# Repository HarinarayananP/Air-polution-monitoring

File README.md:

# Polmo - Air Pollution Monitoring System

POLMO is a low cost IoT based real time air pollution monitoring system. It uses advanced sensing technologies to collect pollution information from the real world sensors and provides real time data visualization, machine learning based air quality prediction, warning information for human beings, animals, and plants due to air pollution.
## Contents

- [Polmo - Air Pollution Monitoring System](#polmo---air-pollution-monitoring-system)
  - [Contents](#contents)
  - [Short description](#short-description)
    - [What's the problem?](#whats-the-problem)
    - [How can technology help?](#how-can-technology-help)
    - [The idea](#the-idea)
  - [Demo video](#demo-video)
  - [The architecture](#the-architecture)
  - [Long description](#long-description)
  - [Project roadmap](#project-roadmap)
  - [Getting started](#getting-started)
  - [Live demo](#live-demo)
  - [Applications](#applications)
    - [Mesh Network - Simple application](#mesh-network---simple-application)
    - [Mesh Network - Vehicle Traffic](#mesh-network---vehicle-traffic)
  - [Built with](#built-with)
  - [Contributing](#contributing)
  - [Authors](#authors)
  - [License](#license)
  - [Acknoledgement](#acknoledgement)

## Short description

### What's the problem?

Air pollution adversely affects human health, plant life, and agricultural crop production. Agricultural crops can be injured when exposed to high concentrations of various air pollutants. In a recent study, researchers have analysed 30 years of data on yields of wheat and rice alongside data on air pollution and climate in India and concluded that significant decreases in yield could be attributed to air pollutants.

### How can technology help?

Regular monitoring and controlling air pollution leads to increased yield from agricultural and livestock products. The warning can be given to farmers using pollution related predictions, precautions can be taken to protect plants, plan for the right cultivation time to get more yield.  There is an increased demand for localized IoT enabled automated air pollution monitoring systems which provide air pollution related information for people through an easy interface.  For realizing such a system gas sensors with advanced sensing technologies, IoT, cloud computing, and machine learning can be Incorporated.

### The idea

Developing and deploying low cost, low power, quicker, and real time air pollution monitoring system at pollution affected area. For this, array sensor nodes are developed by incorporating major air pollutants sensors and NodeMCU.  This embedded system uploads the air pollution data to the IBM Watson IoT cloud over Wi-Fi protocol. 

## Demo video

## The architecture

1. Node Mcu from Polmo sensor node reads the sensor readings. 
2. It will send the readings through MQTT Protocol to IBM Watson IOT
3. Using Node Red Flows the readings are fetched from IBM Watson IOT and Stored it into IBM Cloudant DB
4. A public API Endpoint is made using Fast API, It processes and delivers the contents from Cloudant DB to Apps
5. A React Dashboard is created to visualize realtime data.

## Long description

[More detail is available here](./docs/DESCRIPTION.md)

## Project roadmap

The project currently does the following things.
- Sense Major Pollutants.
- Sent readings seperatly to IBM Watson IOT cloud.
- Display Realtime data at Webendpoint
- Provide API to fetch Realtime and historical data.

See below for our past road map before Call for Code 2021 submission.

## Getting started

You can find the details of each section by clicking the image 🖼️ below 🔻 .

## Live demo

By clicking this [link you](https://polmo-react-app.vercel.app/) can visit the live website. 

## Applications
Here are some animations which we are planning to build. 
### Mesh Network - Simple application

### Mesh Network - Vehicle Traffic

## Built with

- [IBM Cloudant](https://cloud.ibm.com/catalog?search=cloudant#search_results) - The NoSQL database used
- [IBM Watson IOT](https://cloud.ibm.com/catalog?search=IOT#search_results) - The Internet of things platform
- [IBM Cloud Foundry](https://cloud.ibm.com/catalog?search=cloud%20foundry#search_results) - The Application Containers

## Contributing

Please read [CONTRIBUTING.md](CONTRIBUTING.md) for details on our code of conduct, and the process for submitting pull requests to us.

## Authors

- **Harinarayanan P** - [GitHub](https://github.com/HarinarayananP)
- **Amjed Ali K** - [GitHub](https://github.com/amjed-ali-k)
- **Sukhdev K** - [GitHub](https://github.com/Sukhdev)

## License

This project is licensed under the Apache 2 License - see the [LICENSE](LICENSE) file for details.

## Acknoledgement

We sincerly inform our gratitudes to
- [Sebastián Ramírez] (https://github.com/tiangolo) - For FastAPI framework
- [Creative Tim] (https://www.creative-tim.com/) - For Argon free dashboard template
- [Webkom] (https://github.com/0wczar/airframe-react) - For a beautiful react Dashboard
- [Freepik] (https://freepik.com) - For design files and templates
- All family, friends, collegues who helped and appreciated us in this journey.

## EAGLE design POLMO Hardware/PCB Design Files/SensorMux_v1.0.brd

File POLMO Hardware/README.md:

# POLMO - Hardware

## Contents
- [POLMO - Hardware](#polmo---hardware)
  - [Contents](#contents)
  - [Code](#code)
  - [Hardware Photo](#hardware-photo)
  - [Designs of Multiple node](#designs-of-multiple-node)
    - [Polmo Rural node](#polmo-rural-node)
    - [Polmo Urban node](#polmo-urban-node)
    - [Indoor Closed Network Polmo node](#indoor-closed-network-polmo-node)

## Code
Node Mcu (ESP8266 1.0) code can be viewed by clicking this [link](./Node%20Mcu%20Code/mqttclient.ino).
You have to update the WiFi credentials in the code shown below.

```cpp
// WiFi Credentials
const char* ssid = "********"; // WiFi SSID
const char* password = "**************"; // WiFi Password
```
Also IBM Watson IOT configshown below.
```cpp
// IBM Watson IOT - Device Credentials
#define ORG "****" 
#define DEVICE_TYPE "*******" 
#define DEVICE_ID "****" 
#define TOKEN "**********" 

```
This code use Non-Secure data communitication. So, after updating the code, Kindly disable the security to Token Authentication on IBM Watson IOT Dashboard.

## Hardware Photo
Below shows the photo of Hardware prototype which we made for testing.
The PCB Design and Schematic Diagrams can be found [here.](/PCB%20Design%20Files)

## Designs of Multiple node
Here show multiple data flow designs for individual Polmo nodes we are going to fabricate. Currently the node connects directly to the IBM Watson IOT platform. But when we scale the nodes into multiple areas or creating a mesh network, All data flow goes through a master node. LoraWan or any other low power networks will be used to connect between Polmo End Nodes and Master nodes. Master nodes will be connected directly to IBM Watson IOT Platform.
Depending upon the type of region, envornaments we have to design and implement diffrent types of end nodes. Mainly there are 3 types of Polmo End nodes
- Polmo Rural node - For Villages, Farmlands, Green Terrains.
- Polmo Urban node - For Cities, Industiral, Crouded areas.
- Polmo Indoor node - For Homes, Factories, Large camps, Reserved areas.

### Polmo Rural node
This node is indented to deploy in less areas like villages, farmlands. There will be only limited number of deployments in a large area. Sensors will only collect data in long intervals and go to sleep mode. Long range low power communication protocols like LoRaWAN will be used to connect this nodes to its master.
<br><br>

### Polmo Urban node
Polmo Urban nodes will be deployed in highly populated, crouded areas where pollution will affect large number of beings. This node will fetch sensor readings in seconds and send to its master node. Urban nodes will be deployed in short range and even a single city will contains multiple nodes. Urban nodes will have much more accuracy and used to display realtime readings.
<br><br>

### Indoor Closed Network Polmo node
Indoor nodes are made for deployment inside homes, factories and industries. It will be used for particular purposes and safety of humans in houses and the workers in factory. These nodes may not have master nodes and will be directly connected to LAN networks. 
<br><br>

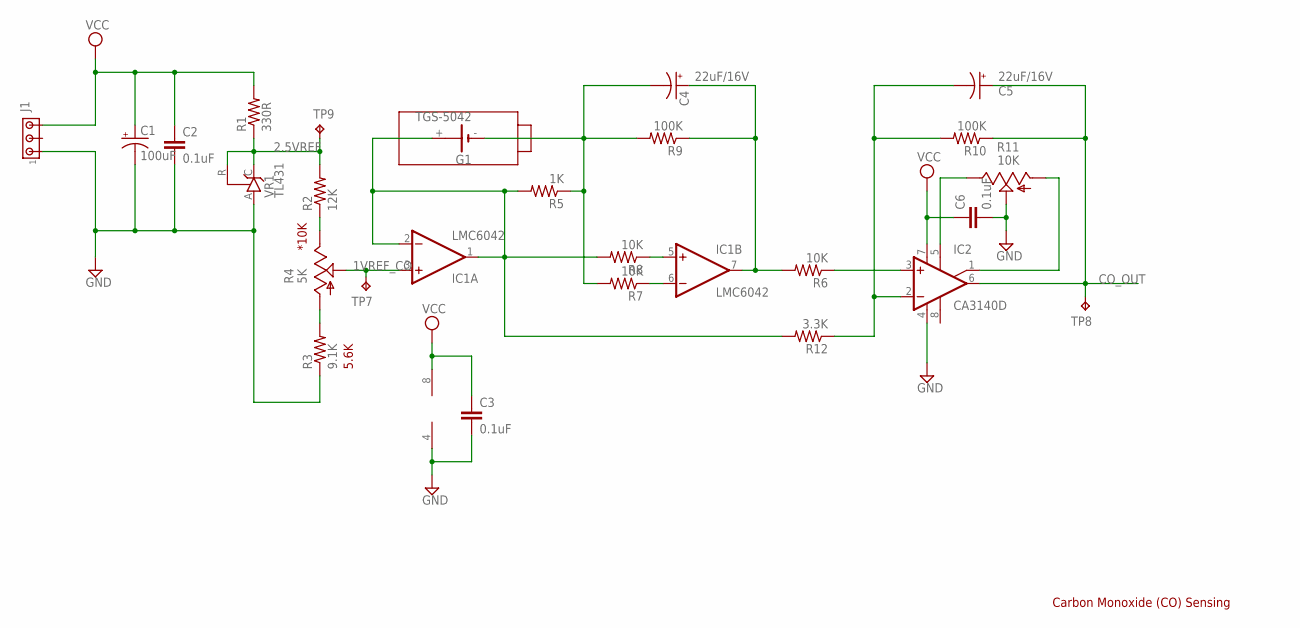
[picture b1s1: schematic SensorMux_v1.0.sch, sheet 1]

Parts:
C1: 100uF; E5-6
C2, C3, C6: 0.1uF; C0603K
C4, C5: 22uF/16V; E2,5-6
G1: TGS-5042; CRAA
IC1: LMC6042; SO08
IC2: CA3140D; SO08
J1: MTA03-100; 10X03MTA
R1: 330R; R0805
R2: 12K; R0805
R3: 9.1K; R0805
R4: 5K; B64Y
R5: 1K; R0805
R6, R7, R8: 10K; R0805
R9, R10: 100K; R0805
R11: 10K; B64Y
R12: 3.3K; R0805
TP7: 1V; TP08R
TP8: CO; TP08R
TP9: 2.5V; TP08R
VR1: TL431; TO92-CLP

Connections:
1VREF_CO: IC1.3 (+IN), R4.S, TP7.TP
2.5VREF: R1.1, R2.2, TP9.TP, VR1.C, VR1.R; also elsewhere on the board
CO_OUT: C5.+, IC2.6 (OUT), R10.1, TP8.TP; also elsewhere on the board
GND: C1.-, C2.2, C3.2, C6.2, IC1.4 (V-), IC2.4 (V-), J1.1, R3.1, R11.S, VR1.A; also elsewhere on the board
unnamed: G1.+, IC1.1 (OUT), IC1.2 (-IN), R5.2, R8.2, R12.2
unnamed: IC1.6 (-IN), R7.1
unnamed: C4.-, G1.-, R5.1, R7.2, R9.2
unnamed: IC1.5 (+IN), R8.1
unnamed: R2.1, R4.E
unnamed: R3.2, R4.A
unnamed: C4.+, IC1.7 (OUT), R6.2, R9.1
unnamed: IC2.3 (+IN), R6.1
unnamed: C5.-, IC2.2 (-IN), R10.2, R12.1
unnamed: IC2.5 (ON), R11.E
unnamed: IC2.1 (ON/CMP), R11.A
VCC: C1.+, C2.1, C3.1, C6.1, IC1.8 (V+), IC2.7 (V+), J1.3, R1.2; also elsewhere on the board

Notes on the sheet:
Carbon Monoxide (CO) Sensing
5.6K
*10K

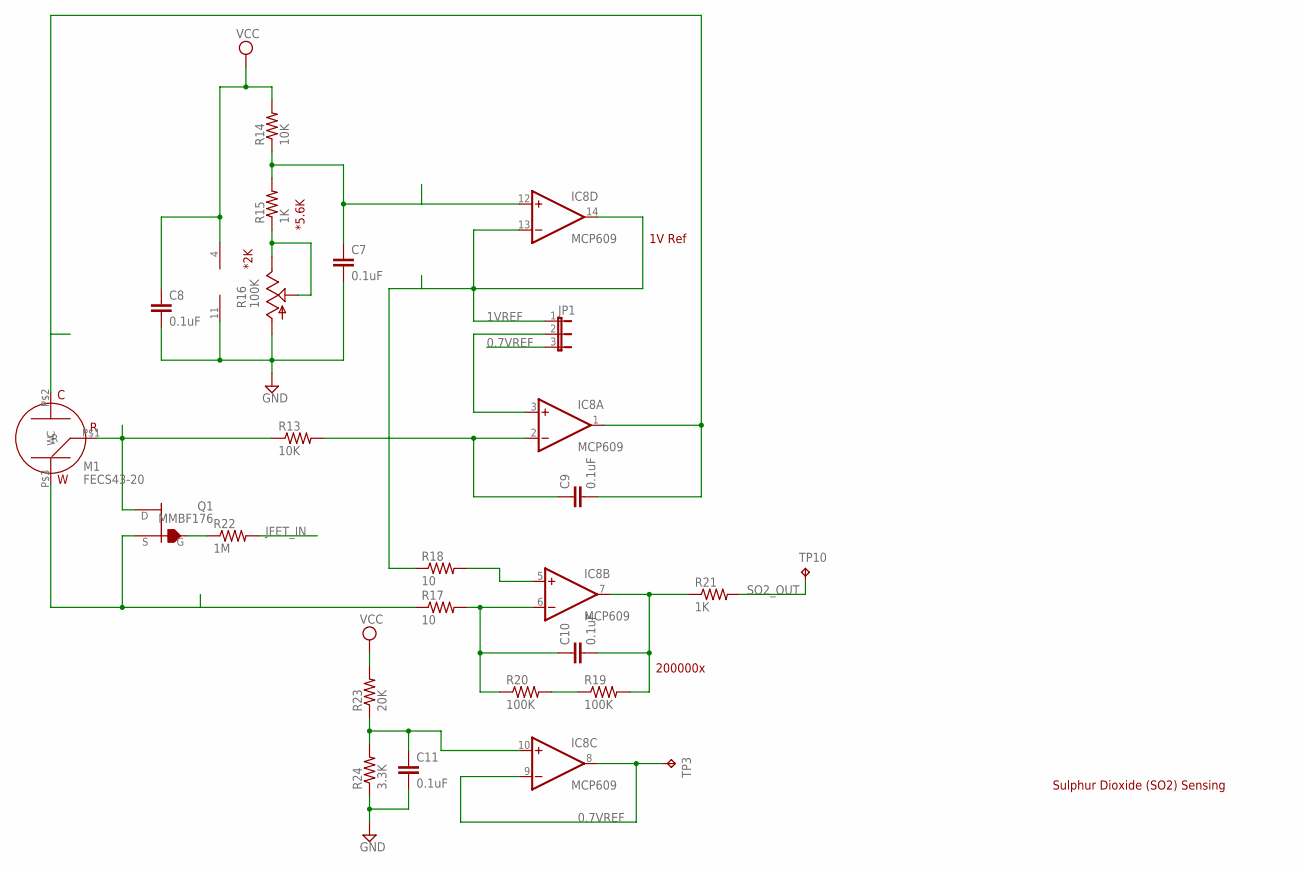
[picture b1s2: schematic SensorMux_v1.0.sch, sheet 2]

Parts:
C7, C8, C9, C10, C11: 0.1uF; C0603K
IC8: MCP609; SO14
JP1: JP2E; JP2
M1: FECS43-20; FECS43
Q1: MMBF176; SOT23
R13: 10K; R0603
R14: 10K; R0805
R15: 1K; R0805
R16: 100K; B64Y
R17, R18: 10; R0603
R19, R20: 100K; R0603
R21: 1K; R0603
R22: 1M; R0603
R23: 20K; R0805
R24: 3.3K; R0805
TP3: 0.7V; TP08R
TP10: SO2; TP08R

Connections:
0.7V: C11.1, IC8.10 (+IN), R23.1, R24.2
0.7VREF: IC8.8 (OUT), IC8.9 (-IN), JP1.3, TP3.TP
1VREF: IC8.13 (-IN), IC8.14 (OUT), JP1.1, R18.1
GND: C7.2, C8.2, C11.2, IC8.11 (V-), R16.A, R24.1; also elsewhere on the board
JFET_IN: R22.2; also elsewhere on the board
unnamed: C9.1, IC8.2 (-IN), R13.2
unnamed: M1.P$1 (R), Q1.1 (D), R13.1
unnamed: C9.2, IC8.1 (OUT), M1.P$2 (C)
unnamed: R15.1, R16.E, R16.S
unnamed: R19.1, R20.2
unnamed: C7.1, IC8.12 (+IN), R14.1, R15.2
unnamed: IC8.3 (+IN), JP1.2
unnamed: C10.1, IC8.6 (-IN), R17.2, R20.1
unnamed: IC8.5 (+IN), R18.2
unnamed: M1.P$3 (W), Q1.2 (S), R17.1
unnamed: C10.2, IC8.7 (OUT), R19.2, R21.1
unnamed: Q1.3 (G), R22.1
SO2_OUT: R21.2, TP10.TP; also elsewhere on the board
VCC: C8.1, IC8.4 (V+), R14.2, R23.2; also elsewhere on the board

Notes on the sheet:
1V Ref
200000x
Sulphur Dioxide (SO2) Sensing
*5.6K
*2K

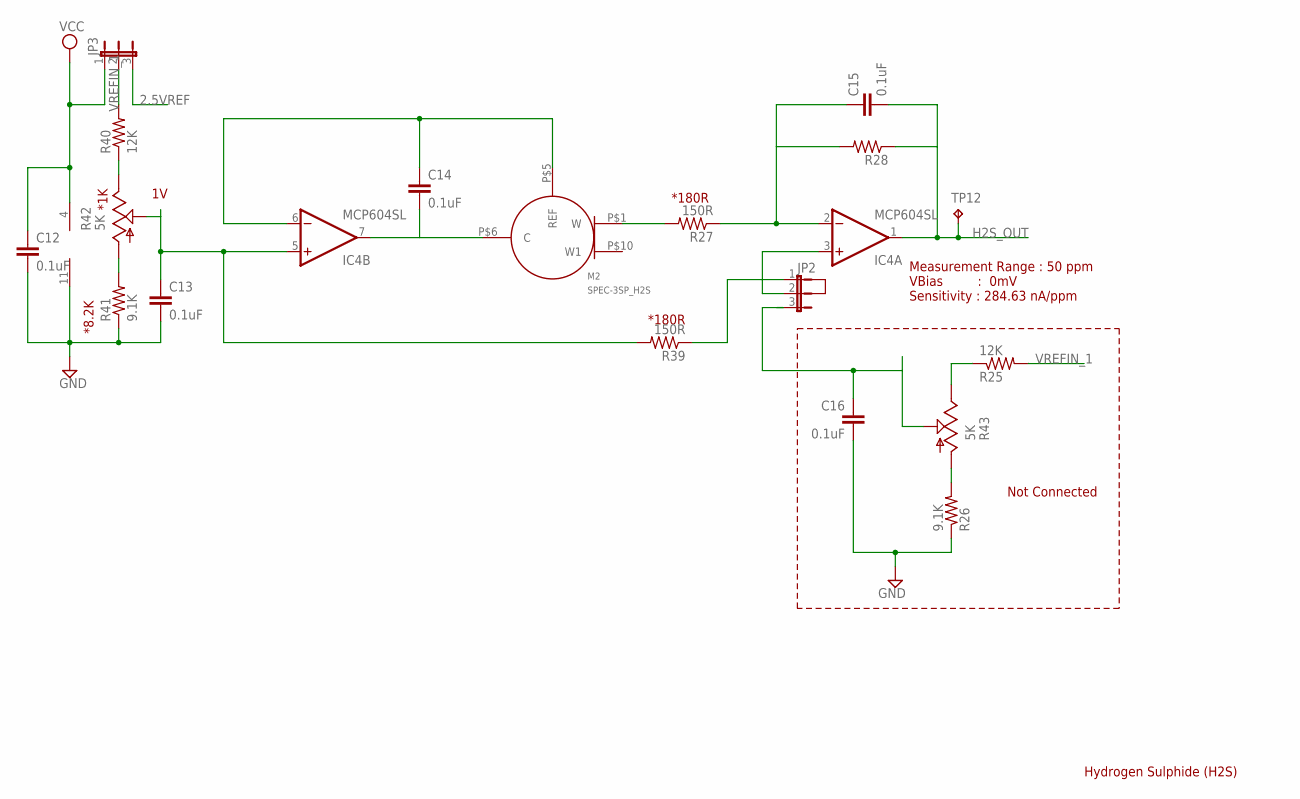
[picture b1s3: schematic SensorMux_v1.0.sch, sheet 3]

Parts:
C12, C13, C14, C15, C16: 0.1uF; C0603K
IC4: MCP604SL; SO14
JP2, JP3: JP2E; JP2
M2: SPEC-3SP_H2S; SPEC-3SP
R25, R40: 12K; R0805
R26, R41: 9.1K; R0805
R27, R39: 150R; R0805
R28: R-US_R0805; R0805
R42, R43: 5K; B64Y
TP12: H2S; TP08R

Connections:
2.5VREF: JP3.3; also elsewhere on the board
GND: C12.2, C13.2, C16.2, IC4.11 (V-), R26.1, R41.1; also elsewhere on the board
H2S_OUT: C15.2, IC4.1 (OUT), R28.1, TP12.TP; also elsewhere on the board
unnamed: C14.1, IC4.6 (-IN), M2.P$5 (REF)
unnamed: C14.2, IC4.7 (OUT), M2.P$6 (C)
unnamed: C13.1, IC4.5 (+IN), R39.2, R42.S
unnamed: M2.P$1 (W), R27.2
unnamed: C15.1, IC4.2 (-IN), R27.1, R28.2
unnamed: C16.1, JP2.3, R43.S
unnamed: IC4.3 (+IN), JP2.2
unnamed: R25.1, R43.E
unnamed: R26.2, R43.A
unnamed: JP2.1, R39.1
unnamed: R40.1, R42.E
unnamed: R41.2, R42.A
VCC: C12.1, IC4.4 (V+), JP3.1; also elsewhere on the board
VREFIN_1: JP3.2, R25.2, R40.2

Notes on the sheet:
Hydrogen Sulphide (H2S)
Measurement Range : 50 ppm VBias : 0mV Sensitivity : 284.63 nA/ppm
*180R
*8.2K
*1K
Not Connected

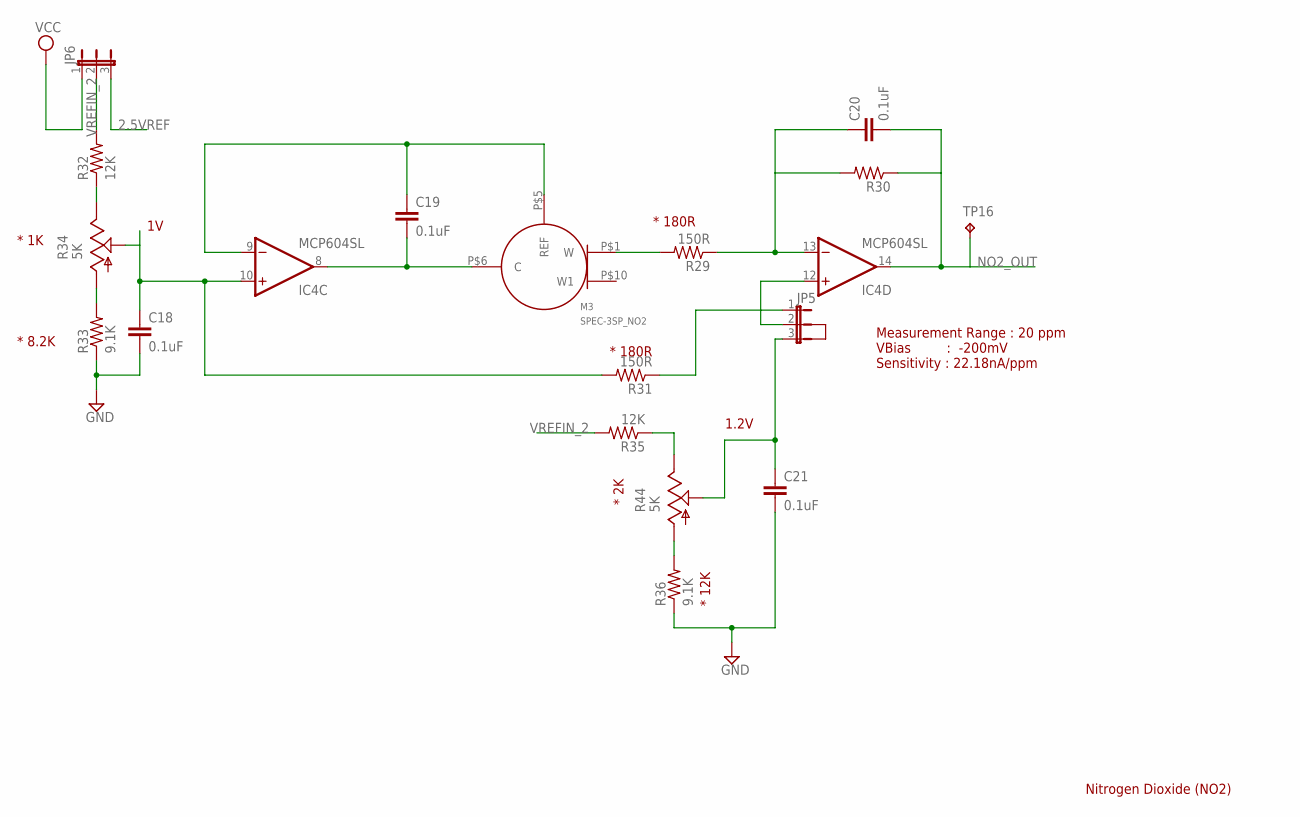
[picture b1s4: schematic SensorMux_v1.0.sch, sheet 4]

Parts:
C18, C19, C20, C21: 0.1uF; C0603K
IC4: MCP604SL; SO14
JP5, JP6: JP2E; JP2
M3: SPEC-3SP_NO2; SPEC-3SP
R29, R31: 150R; R0805
R30: R-US_R0805; R0805
R32, R35: 12K; R0805
R33, R36: 9.1K; R0805
R34, R44: 5K; B64Y
TP16: NO2; TP08R

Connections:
2.5VREF: JP6.3; also elsewhere on the board
GND: C18.2, C21.2, R33.1, R36.1; also elsewhere on the board
unnamed: C19.1, IC4.9 (-IN), M3.P$5 (REF)
unnamed: C19.2, IC4.8 (OUT), M3.P$6 (C)
unnamed: C18.1, IC4.10 (+IN), R31.2, R34.S
unnamed: M3.P$1 (W), R29.2
unnamed: C20.1, IC4.13 (-IN), R29.1, R30.2
unnamed: C21.1, JP5.3, R44.S
unnamed: IC4.12 (+IN), JP5.2
unnamed: JP5.1, R31.1
unnamed: R32.1, R34.E
unnamed: R33.2, R34.A
unnamed: R35.1, R44.E
unnamed: R36.2, R44.A
NO2_OUT: C20.2, IC4.14 (OUT), R30.1, TP16.TP; also elsewhere on the board
VCC: JP6.1; also elsewhere on the board
VREFIN_2: JP6.2, R32.2, R35.2

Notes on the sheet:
Nitrogen Dioxide (NO2)
Measurement Range : 20 ppm VBias : -200mV Sensitivity : 22.18nA/ppm
* 1K
* 8.2K
* 12K
* 2K
1.2V
* 180R

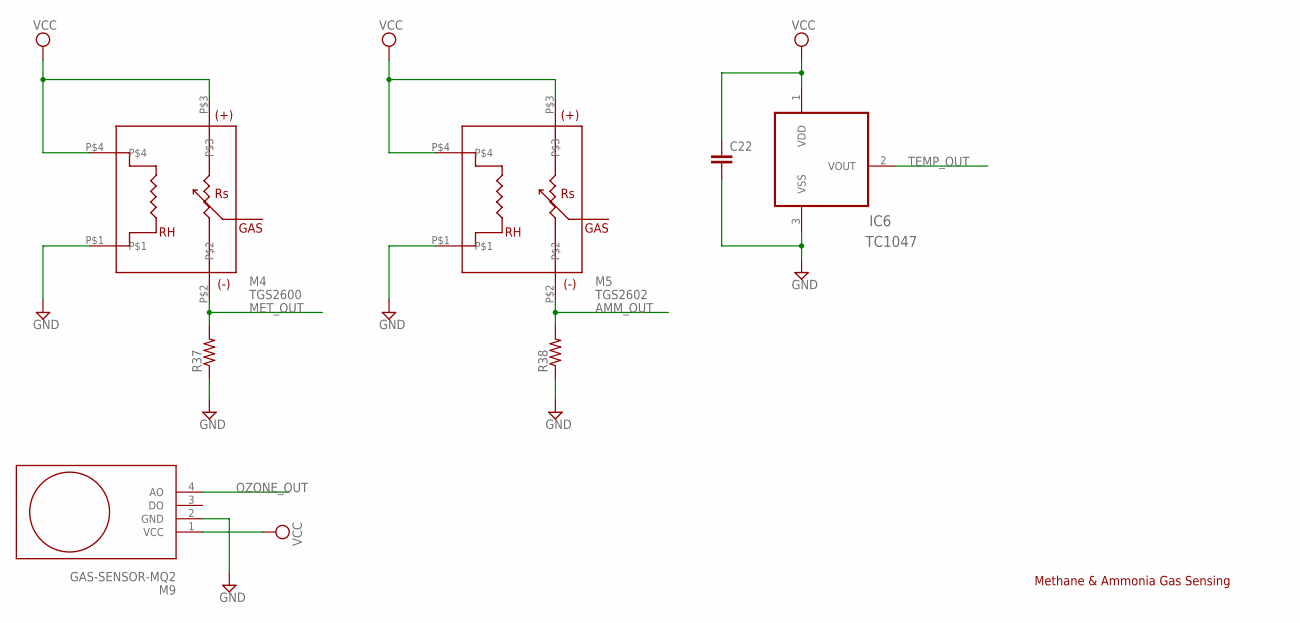
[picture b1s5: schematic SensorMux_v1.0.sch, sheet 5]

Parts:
C22: C-EUC0603K; C0603K
IC6: TC1047; SOT95P237X112-3N
M4: TGS2600; TGS26XX
M5: TGS2602; TGS26XX
M9: GAS-SENSOR-MQ2
R37, R38: R-US_M0805; M0805

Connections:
AMM_OUT: M5.P$2, R38.2; also elsewhere on the board
GND: C22.2, IC6.3 (VSS), M4.P$1, M5.P$1, M9.2 (GND), R37.1, R38.1; also elsewhere on the board
MET_OUT: M4.P$2, R37.2; also elsewhere on the board
OZONE_OUT: M9.4 (AO); also elsewhere on the board
TEMP_OUT: IC6.2 (VOUT); also elsewhere on the board
VCC: C22.1, IC6.1 (VDD), M4.P$3, M4.P$4, M5.P$3, M5.P$4, M9.1 (VCC); also elsewhere on the board

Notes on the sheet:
Methane & Ammonia Gas Sensing

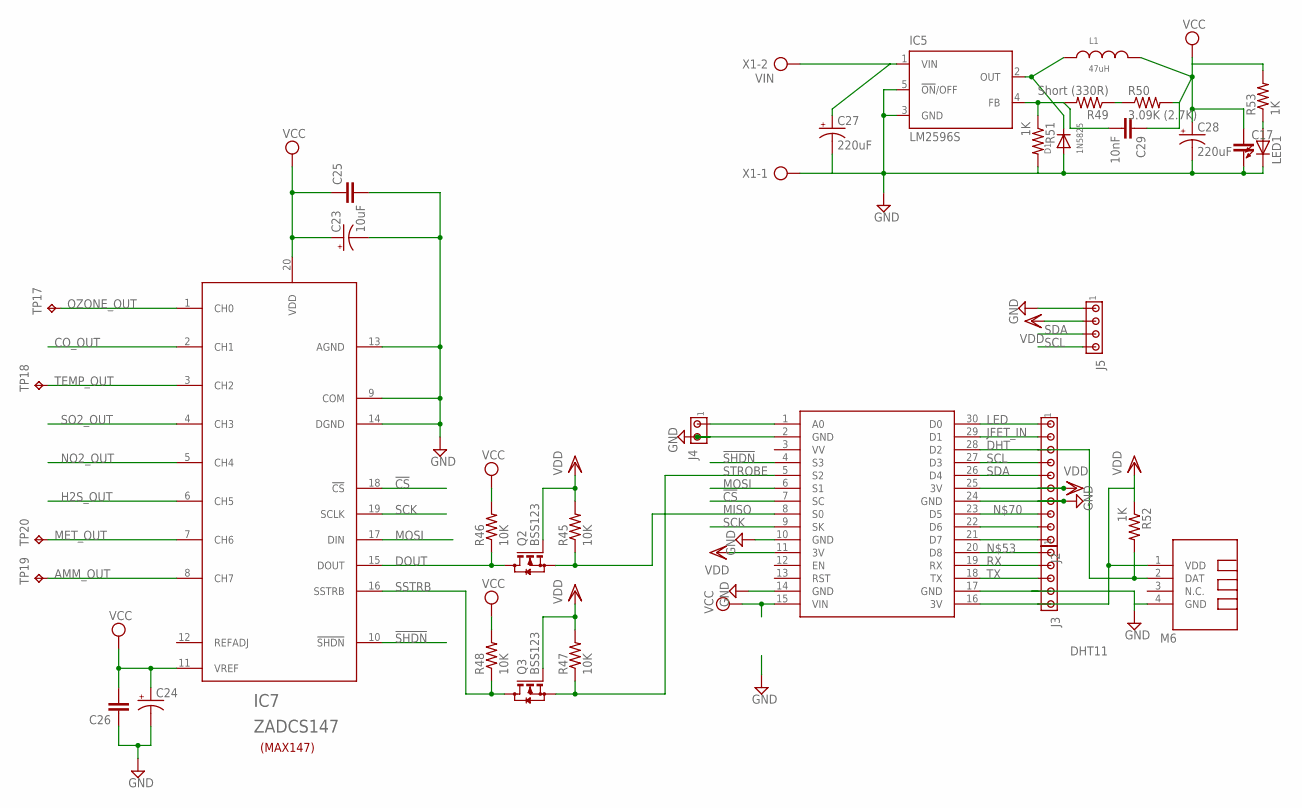
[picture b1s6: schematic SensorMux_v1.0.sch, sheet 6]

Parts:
C17, C25, C26: C-EUC0603K; C0603K
C23: 10uF; SMC_A
C24: CPOL-USSMCA; SMC_A
C27, C28: 220uF; 140CLH-0810
C29: 10nF; C0603K
D1: 1N5825; SMADIODE
IC5: LM2596S; TO263-5
IC7: ZADCS147; SSOP20
J2: MTA10-100; 10X10MTA
J3: MTA05-100; 10X05MTA
J4: MTA02-100; 10X02MTA
J5: MTA04-100; 10X04MTA
L1: 47uH; WE-CHSA_1212
LED1: LED3MM
M6: DHT11; TEMP-HUM-SENSOR-DHT11
M8: NODEMCU
Q2, Q3: BSS123; SOT23
R45, R46, R47, R48: 10K; R0603
R49: Short (330R); R0603
R50: 3.09K (2.7K); R0603
R51, R52, R53: 1K; R0603
TP17: Ozone; TP08R
TP18: Temp; TP08R
TP19: AMM; TP08R
TP20: MET; TP08R
X1: VIN; AK500/2

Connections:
!CS: IC7.18 (!CS), M8.7 (SC)
!SHDN: IC7.10 (!SHDN), M8.4 (S3)
AMM_OUT: IC7.8 (CH7), TP19.TP; also elsewhere on the board
CO_OUT: IC7.2 (CH1); also elsewhere on the board
DHT: J2.3, M6.2 (DAT), M8.28 (D2), R52.2
DOUT: IC7.15 (DOUT), Q2.3 (D), R46.1
GND: C17.2, C23.-, C24.-, C25.2, C26.1, C27.-, C28.-, D1.A, IC5.3 (GND), IC5.5 (!ON!/OFF), IC7.9 (COM), IC7.13 (AGND), IC7.14 (DGND), J2.7, J4.2, J5.1, LED1.K (C), M6.4 (GND), M8.2 (GND), M8.10 (GND), M8.14 (GND), M8.24 (GND), R51.2, X1.1; also elsewhere on the board
H2S_OUT: IC7.6 (CH5); also elsewhere on the board
JFET_IN: J2.2, M8.29 (D1); also elsewhere on the board
LED: J2.1, M8.30 (D0)
MET_OUT: IC7.7 (CH6), TP20.TP; also elsewhere on the board
MISO: M8.8 (S0), Q2.2 (S), R45.1
MOSI: IC7.17 (DIN), M8.6 (S1)
unnamed: J3.1, M8.20 (D8)
unnamed: LED1.A, R53.1
unnamed: R49.1, R50.1
unnamed: J2.8, M8.23 (D5)
unnamed: J2.9, M8.22 (D6)
unnamed: J2.10, M8.21 (D7)
unnamed: J3.4, M8.17 (GND)
unnamed: J4.1, M8.1 (A0)
NO2_OUT: IC7.5 (CH4); also elsewhere on the board
OUT: D1.C, IC5.2 (OUT), L1.1
OZONE_OUT: IC7.1 (CH0), TP17.TP; also elsewhere on the board
RX: J3.2, M8.19 (RX)
SCK: IC7.19 (SCLK), M8.9 (SK)
SCL: J2.4, J5.4, M8.27 (D3)
SDA: J2.5, J5.3, M8.26 (D4)
SO2_OUT: IC7.4 (CH3); also elsewhere on the board
SSTRB: IC7.16 (SSTRB), Q3.3 (D), R48.1
STROBE: M8.5 (S2), Q3.2 (S), R47.1
TEMP_OUT: IC7.3 (CH2), TP18.TP; also elsewhere on the board
TX: J3.3, M8.18 (TX)
VCC: C17.1, C23.+, C24.+, C25.1, C26.2, C28.+, C29.1, IC7.11 (VREF), IC7.20 (VDD), L1.2, M8.15 (VIN), R46.2, R48.2, R50.2, R53.2; also elsewhere on the board
VDD: J2.6, J3.5, J5.2, M6.1 (VDD), M8.11 (3V), M8.16 (3V), M8.25 (3V), Q2.1 (G), Q3.1 (G), R45.2, R47.2, R52.1
VFBK: C29.2, IC5.4 (FB), R49.2, R51.1
VIN: C27.+, IC5.1 (VIN), X1.2

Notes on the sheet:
(MAX147)

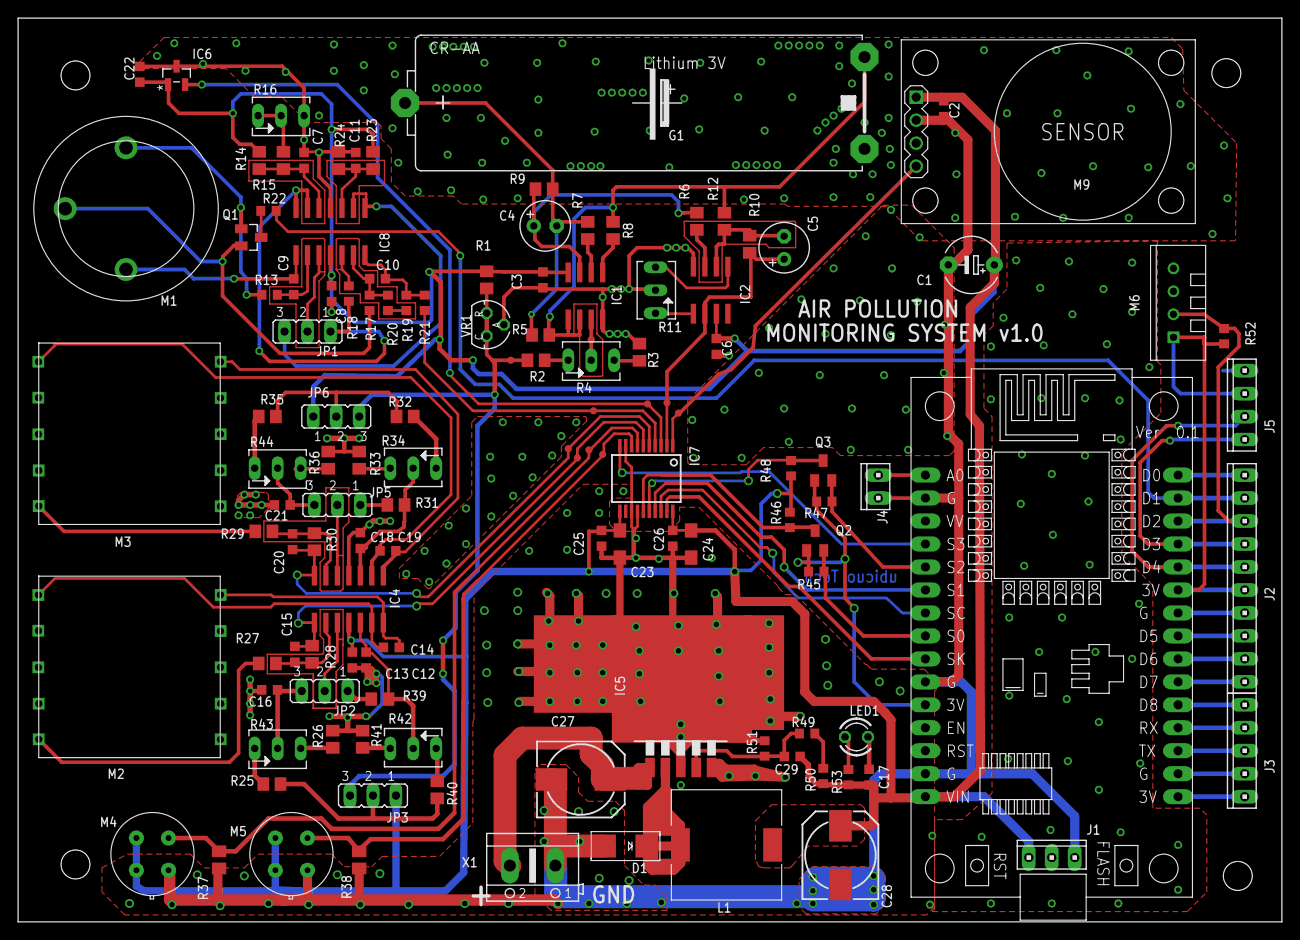
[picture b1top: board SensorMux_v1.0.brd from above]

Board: 2 copper layers, 139.8 x 99.9 mm, 127 parts (0 on the bottom side), 91 nets.

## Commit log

2021-07-31 Uploaded Roadmap
2021-07-31 Updated Road Maps
2021-07-31 Uploaded Youtube Thimbnail
2021-08-01 Updated Project files
2021-08-01 Updated Endpoints
2021-08-01 Updated Endpoints and Docs
2021-08-03 Updated Polmo api endpoint Readme
2021-08-03 Updated Frontend App
2021-08-05 Added Node-Red Flows
2021-08-05 Added Hardware Photo
2021-08-05 Fixed Bug
2021-08-05 Updated Files From Repositories
2021-08-06 Restructured for Roadmap Update
2021-08-06 Updated Description on Polmo Hardware Readme. Added Rural Sensor node dataflow
2021-08-06 Added Urban Node details and Data flow
2021-08-06 Added details and Data flow about indoor nodes
2021-08-06 Updated Software Readme
2021-08-06 Rename blank.yml to telegram_notification.yml
2021-08-07 Added Applicatoin Gifs
2021-10-06 Updated Youtube Link
    As per request from IBM, new Video is uploaded by clearing all known legal issues. Removed IBM Watson Logo and IBM Cloudant DB Logo.
2021-10-06 Typo Fixes

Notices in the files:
README.md:
License: Apache2
parts and their libraries:
diy-modules: Released under the Creative Commons Attribution 4.0 International License: http://creativecommons.org/licenses/by/4.0
EMCComponents: Copyright: Würth Elektronik
